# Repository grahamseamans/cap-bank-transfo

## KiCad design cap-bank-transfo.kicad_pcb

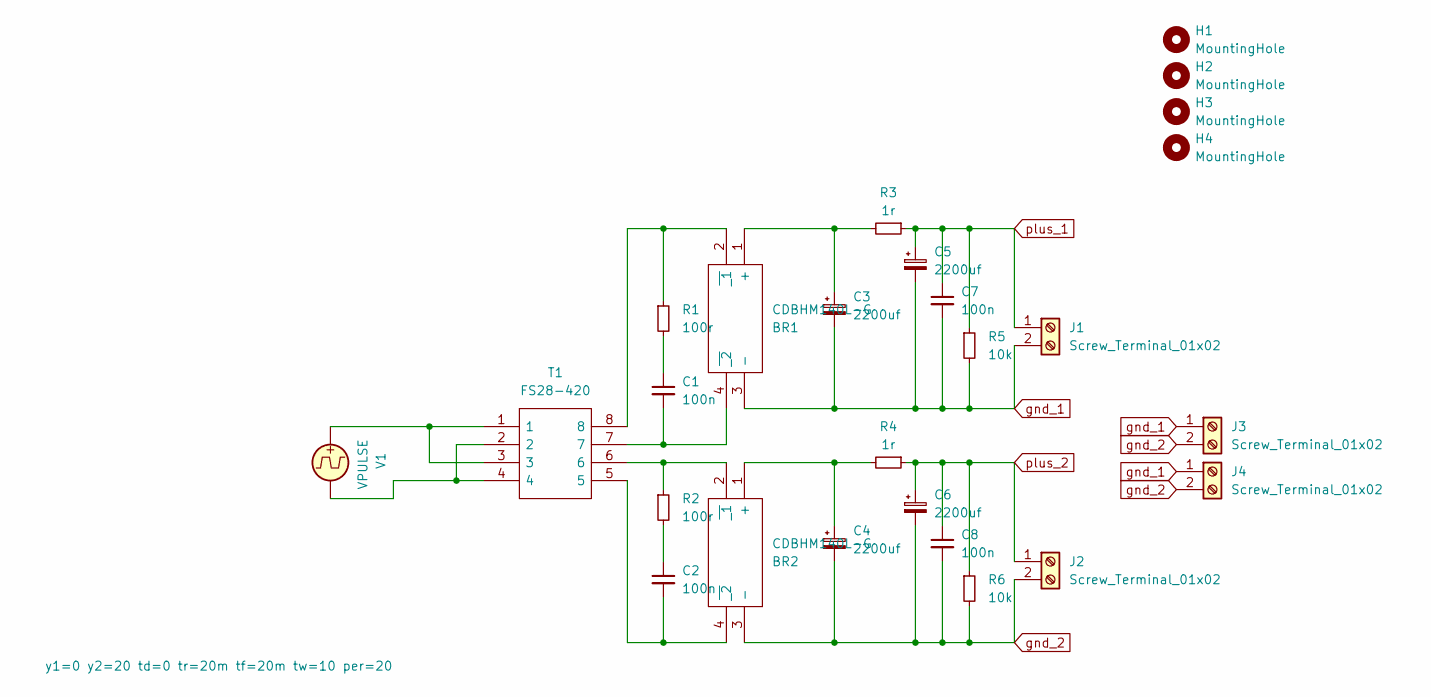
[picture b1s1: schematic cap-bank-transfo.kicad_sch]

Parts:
BR1, BR2: CDBHM140L-G; CDBHM140LG; Mouser Part Number 750-CDBHM140L-G
C1, C2, C7, C8: 100n; C_Rect_L7.2mm_W2.5mm_P5.00mm_FKS2_FKP2_MKS2_MKP2
C3, C4, C5, C6: 2200uf; CP_Radial_D12.5mm_P5.00mm
H1, H2, H3, H4: MountingHole; MountingHole_3.2mm_M3_ISO7380
J1, J2: Screw_Terminal_01x02; 395443002
J3, J4: Screw_Terminal_01x02; PinHeader_1x02_P2.54mm_Vertical
R1, R2: 100r; R_1206_3216Metric
R3, R4: 1r; R_1206_3216Metric
R5, R6: 10k; R_1206_3216Metric
T1: FS28-420; FS28420; Mouser Part Number 553-FS28-420
V1: VPULSE; 395443002

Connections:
unnamed: BR1.1 (+), C3.1, R3.2
unnamed: BR1.2 (~_1), R1.1, T1.8
unnamed: BR1.4 (~_2), C1.2, T1.7
unnamed: BR2.1 (+), C4.1, R4.2
unnamed: BR2.2 (~_1), R2.1, T1.6
unnamed: BR2.4 (~_2), C2.2, T1.5
unnamed: C1.1, R1.2
unnamed: C2.1, R2.2
unnamed: T1.1, T1.3, V1.1
unnamed: T1.2, T1.4, V1.2
gnd_1: BR1.3 (-), C3.2, C5.2, C7.2, J1.2, J3.1, J4.1, R5.2
gnd_2: BR2.3 (-), C4.2, C6.2, C8.2, J2.2, J3.2, J4.2, R6.2
plus_1: C5.1, C7.1, J1.1, R3.1, R5.1
plus_2: C6.1, C8.1, J2.1, R4.1, R6.1

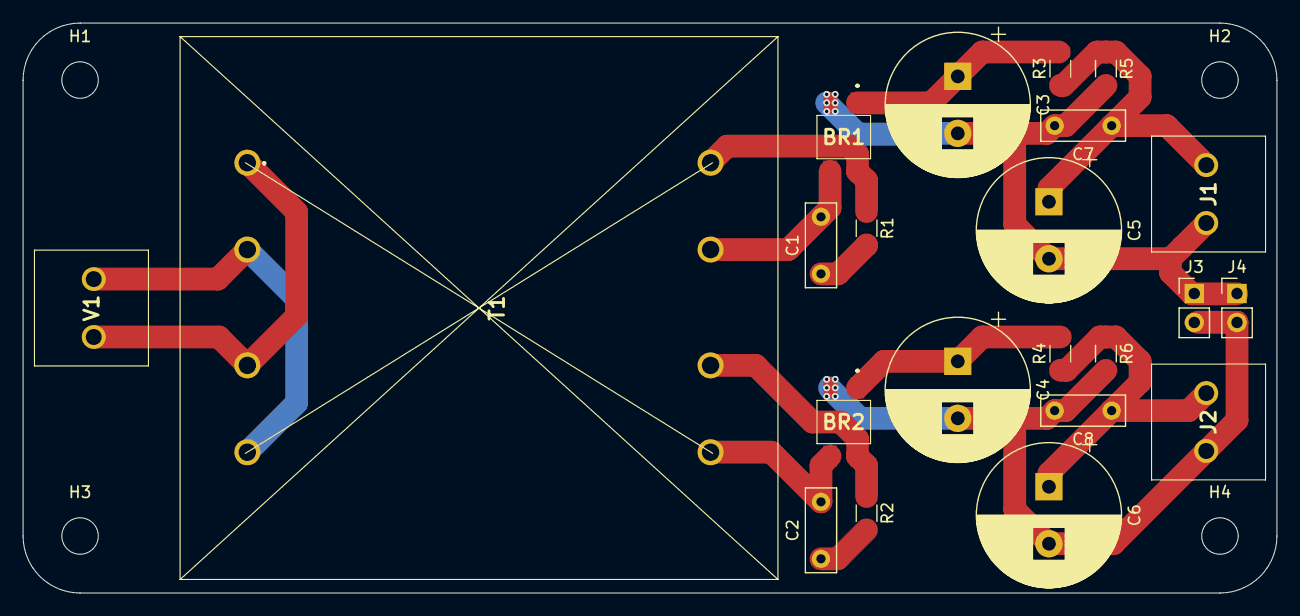
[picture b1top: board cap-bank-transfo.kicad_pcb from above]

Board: 2 copper layers, 110.0 x 50.0 mm, 26 parts (0 on the bottom side), 14 nets.

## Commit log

2025-01-05 added second header for ground jumpers
